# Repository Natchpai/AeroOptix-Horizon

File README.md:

**Flight controller for the AeroOptix Club aircraft, STM32H743 with an STM32F100 IO MCU**

> **Status:** `PRELIMINARY`
> **Board revision:** `A`
> **Baseline:** `NOT_ESTABLISHED`
> **KiCad:** `10.0.8`

> **Draft specification (rev 0.95, 2026-11-28): NOT FOR FABRICATION.** Everything below is a design target from the specification, not a verified result. Values not yet decided are shown as `TBD`.

## Overview

AeroOptix-Horizon is a custom PX4 flight controller with two MCUs. The STM32H743VIT6 runs the flight stack and drives the 4 tilt servo outputs. The STM32F100C8T6B runs px4io and drives the 4 ESC outputs, the 4 control-surface servo outputs, the safety switch and the output failsafe (DEC-050, DEC-051).

Pixhawk 6C and 6X are functional references only; their schematics and PCBs are not copied. H743 pins mostly follow `px4/fmu-v6c`, F100 pins follow `px4/io-v2` (DEC-014).

The team website, [natchpai.github.io/AeroOptix-Horizon](https://natchpai.github.io/AeroOptix-Horizon/), shows the block diagram, the MCU pinouts and the status, built from the design records.

## Key Features

- STM32H743VIT6 flight MCU and STM32F100C8T6B px4io MCU, linked over USART at 1.5 Mb/s
- 4 ESC outputs (MAIN 1 to 4) and 4 control-surface outputs (MAIN 5 to 8) on the F100, 4 tilt servo outputs (AUX 1 to 4) on the H743; 8 servo headers on an on-board 6 V rail, 3 spare outputs
- 2× ICM-45686 IMU on SPI; ICP-20100 and BMP581 barometers and IST8310 magnetometer on I2C
- 5 V input through a TPS2121 power mux (power module or USB), 3.3 V buck, separate LDO for the sensor VDD pins
- USB FS, microSD, debug access to both MCUs, BOOT0 push button on the H743

## Specifications

| Parameter | Specification |
|---|---|
| Main MCU | STM32H743VIT6 (DEC-001) |
| IO MCU | STM32F100C8T6B (px4io, DEC-002) |
| Clocks | H743 16 MHz, F100 24 MHz, both from CMOS oscillators (DEC-017, DEC-044) |
| Outputs | F100 MAIN 1 to 4: 4 ESCs (PWM, 1000 to 2000 µs); F100 MAIN 5 to 8: 4 control surfaces (50 Hz PWM); H743 AUX 1 to 4: 4 tilt servos; 3 spare (H743) (DEC-050, DEC-051, FUN-002, FUN-003, IF-017 to IF-019) |
| Sensors | 2× ICM-45686, ICP-20100 + BMP581 (BMP384 fallback), IST8310 (DEC-008, DEC-010, DEC-011) |
| Board input | 5 V, 4.5 to 5.5 V, 2 A source; power mux limit 1.5 A; overvoltage cut-off 5.5 to 6.2 V (PWR-010, DEC-029, DEC-030, DEC-036, DEC-055) |
| 3.3 V rails | `+3V3` buck, design current about 0.6 A (DEC-012, DEC-040); `+3V3A` LDO for the sensor VDD pins; sensor VDDIO on `+3V3` (DEC-043, DEC-027) |
| Servo supply | Two rails, `+VSERVO1` (4 tilt servos) and `+VSERVO2` (4 surface servos), 6 to 8.4 V each; the DS3235 above its 7.4 V rating is accepted (PWR-011, DEC-110, DEC-113). One UBEC per rail (DEC-114), each through a 1x3 header, CN804 and CN805; XT30 removed (DEC-111). Stall at 6 V about 8.4 A and 4.8 A per rail, `ESTIMATED`; one header pin per rail, rating not checked, accepted (DEC-113). Bulk 112 µF nominal per rail (DEC-097, DEC-109); SMF8.5A TVS per rail (DEC-112); copper and GND join set at layout (OPEN-021) |
| Board outline | Under 80 mm each side; exact outline `TBD` (MEC-001, OPEN-009) |
| Mounting | M3, 3.2 mm holes, soft mount; pattern `TBD` (MEC-002, OPEN-009) |
| Layers / stackup | Drawn, not decided: 4 copper layers, about 1.6 mm, 0.1 mm track and clearance (PCB-001 to PCB-005, OPEN-040) |
| Temperature | Parts rated −40 to +85 °C (ENV-001, DEC-020) |

*Specifications describe design targets unless explicitly identified as measured or verified results.*

## Project Status

**Current Phase:** `PRELIMINARY`

| Phase | Description |
|---|---|
| DRAFT | Schematic design in progress |
| PRELIMINARY | Schematic nearly complete; PCB design started |
| CHECK | Design mostly finalized; human-led verification |
| RELEASE | Human-approved design baseline released |

*The project owner declares the current phase. It does not independently establish design correctness or approval.*

### Project Workflow Diagram

```mermaid
flowchart LR
    A["DRAFT<br/>Schematic Design"]
    B["PRELIMINARY<br/>Schematic Finalization<br/>PCB Design"]
    C["CHECK<br/>Design Docs<br/>ERC / DRC<br/>Human Review"]
    D["RELEASE<br/>Approved Design<br/>Baseline Publication"]

    A --> B
    B --> C
    C --> D

    classDef inactive fill:#334155,color:#ffffff,stroke:#64748b
    classDef review fill:#b45309,color:#ffffff,stroke:#92400e
    classDef done fill:#15803d,color:#ffffff,stroke:#166534

    class A done
    class B review
    class C inactive
    class D inactive
```

> Slate: not started, Amber: current phase, Green: completed

The diagram is for reference only. It does not enforce gates or approve releases.

### Design progress

State of the saved KiCad files (2026-11-21 11:12 save, commit `3c111fc`). Sheets not listed have no parts. Part lists, references and save dates are in specification 4.2 "Schematic state", 4.3 and 4.6. Pin allocation `ALLOCATED`, not `VERIFIED` (P1 closed by the human owner, 2026-11-21).

| Area | State |
|---|---|
| Power sheet | Drawn; human ERC and a `sch-review` of the 2026-11-03 save are under Verification; LCSC codes on all resistors; PR1, CP2 and OV bottom resistors 5.1 kΩ, OV trip 5.51 to 6.21 V (DEC-055); MFR, MFR.P/N and LCSC filled on R101 to R115 (P2-021 done 2026-11-21; 1 % tolerance `ASSUMED`); DNP Plan B diodes D105 and D106 replace U101 when it is not fitted (DEC-108, OPEN-041). |
| MCU sheets | In capture; one shared reset with one button decided; B901 PTS815SJM250SMTRLFS checked against LCSC C2689510, reset bench check open (DEC-046, OPEN-026); BOOT0 push button B902 to `+3V3` with R202 10 kΩ to `GND`, and F100 PB2 (BOOT1) without a resistor (DEC-095); separate NRST nets for each MCU behind D201 and D301, joined at B901 (DEC-074); board LEDs driven straight from the pins, active low, 220 Ω (DEC-067); F100 px4io LEDs (blue, red, green) and 10 kΩ pull-ups on PA10 and PB11 (DEC-079); the six LEDs are now two RGB LEDs, D901 (H743) and D902 (F100) (DEC-115); microSD 10 kΩ pull-ups on CMD and DAT0 to DAT3, no card detect (DEC-078), 100 nF and 2.2 µF at the card supply (DEC-081); oscillator parts decided and their data meets both MCU HSE bypass limits (DEC-048, CMP-010); LCSC codes match the part numbers (CMP-010); U302 clock margins accepted (DEC-089); VREF+ tied to VDDA with 2.2 µF (DEC-049, DEC-063); F100 VDDA 22 Ω with 2.2 µF and 100 nF (DEC-101); no ESD on microSD (DEC-104); stub labels on unused pins kept (DEC-105); all allocated pins labelled with DEC-052 net names and every sheet pin matching its label; the INFO names accepted as drawn (OPEN-032 closed); resistors renumbered without gaps (spec rev 0.75); servo-rail divider on `conn-actuator` decided (DEC-066); H743 battery ADC inputs removed, battery data comes from the PM02D only (DEC-107). |
| Sensor sheets | In capture with all five sensors; IST8310 at 0x0C as strapped (DEC-047, closes OPEN-027). ICM-45686 RESV pin 7 not connected (DEC-082); BMP581 INT through 10 kΩ to `GND`, ICP-20100 INT not connected (DEC-083); ICP-20100 power-up order accepted, bench check (DEC-085). I2C2 pull-ups R501 and R502 2 kΩ, bus at 400 kHz (DEC-094, DEC-100); U503 placed as far as possible from the power parts (DEC-096). Address straps are direct ties, no strap resistors: AD0 and SDO through net ties NT501 and NT502 to `GND`, CAD0 and CAD1 to `GND`, BMP581 CSB to `+3V3`; addresses 0x63, 0x46, 0x0C (DEC-099). One 100 nF per sensor supply pin, ICM-45686 pins 7 and 9 not connected (DEC-103); IST8310 VPP floating (DEC-102). |
| USB and debug sheet | In capture; MFR, MFR.P/N and LCSC on every BOM part (OPEN-010 closed); CN602 (H743) JST-SH 6-pin in the Pixhawk Debug Mini order, no NRST, reset by B901 (DEC-065); F100 debug on test pads TP601 to TP606, with TP605 on `RESET_B` (DEC-075); USB-C CC resistors 5.1 kΩ; USB nets checked and no `VBUS` back-feed through U101 (P1-006); VBUS sense on PA9 through a 5.1 kΩ / 10 kΩ divider, so PA9 stays under 4 V when the MCU is unpowered (DEC-080); USB ESD is the ST USBLC6-2SC6, LCSC C7519 (DEC-084); the `VBUS` `PWR_FLAG` stays on the power sheet (DEC-105). |
| External connectors | Drawn, not decided (spec 4.2): `conn-peripherals` (TELEM 1 and 2, I2C4, rangefinder, GPS1) linked to the MCU sheets by sheet pins; `conn-actuator` with MAIN 1 to 4 ESC headers (no + pin), AUX 1 to 4 on `+VSERVO1` and MAIN 5 to 8 on `+VSERVO2`, a 1x3 UBEC header per rail (CN804, CN805), bulk capacitors, a TVS and a sense divider per rail (DEC-110 to DEC-113). Decided 2026-11-19: C803 (C801 since the 2026-11-22 10:23 save) 68 µF 16 V tantalum (DEC-058) and D807 SMF7.5A unidirectional TVS (DEC-059; SMF8.5A with D808 since DEC-112). RC IN drawn (2026-11-19 15:25 save): SP3031-01ETG ESD (D708 since the 23:17 save; DEC-071), R715 22 Ω (R714 before the 16:03 save) and the U303 SN74LVC1G34DCKR buffer to F100 PA8 (DEC-056, DEC-057); CN706 is a 1x3 2.54 mm header since the 2026-11-20 save, with pin 1 PPM, 2 `+5V`, 3 `GND`, kept as drawn (DEC-098, amends DEC-072). 100 kΩ pull-downs on all 15 PWM lines (DEC-073). Spare outputs: 22 Ω series, pull-downs and pads CN707 to CN710 drawn (DEC-069, DEC-076). Second 68 µF T495 on `+6V` (DEC-097; C802 since the 10:23 save). 4 × 22 µF 25 V X7R 1210 (C803 to C806) add low-ESR bulk, 224 µF nominal (DEC-109); the servo-rail 100 nF is C809. Connector pinouts match DS-009; CN704 silkscreen left (OPEN-023). |
| PCB | Updated from the schematic by the human owner (2026-11-21, commit `eec3593`, adds D105 and D106; 2026-11-22 09:23 save: Description fields and BOM exclusion on the test pads, solder pads and net ties); not yet updated from the 2026-11-22 10:23 schematic (C801 to C806 and C809, P3-013) or the 2026-11-24 servo rail split (P3-014). First import 2026-11-20 (commit `a70e6cc`, 9 placed inside the working area then); no routing. 4-layer stackup and board rules drawn, not decided (OPEN-040). The 80 × 80 mm `Edge.Cuts` rectangle is a working area, not the board outline (OPEN-009). |
| Library | Project parts for the parts in use. Sensor footprints: IST8310 and BMP581 confirmed by the human owner, with a 30 µm solder mask margin on purpose; ICP-20100 and ICM-45686 match the datasheet body, pitch and pad numbers and are kept without the TDK land-pattern app notes (DEC-086). New: Amass XT30PW-M symbol, footprint and 3D model. MFR and MFR.P/N on the 20 placed, fully specified library symbols; descriptions in one pattern (2026-11-20). |

## Hardware Design

### Architecture

| Block | Role |
|---|---|
| H743 main controller | Flight stack and interface host; 4 tilt servo outputs (AUX 1 to 4) |
| F100 IO controller | px4io: 4 ESC and 4 control-surface outputs (MAIN 1 to 8), safety switch and LED, servo rail sense, output failsafe (DEC-051) |
| Sensors | 2 IMU on SPI1 and SPI4; 2 barometers and the magnetometer on I2C2 |
| External I/O | SiK telemetry radio, RC receiver (PPM, F100), GPS and compass, air-data sensor, rangefinder, power module, motors (one 4in1 ESC), spare output pads, microSD, GPS module buzzer (no board buzzer), LEDs (DEC-053, DEC-054, DEC-056, DEC-057, DEC-068, DEC-069) |
| USB / debug | USB FS; H743 debug connector CN602, console + SWD in the Pixhawk Debug Mini order, no NRST (IF-045, DEC-065); F100 console + SWD on test pads TP601 to TP606 (IF-051, DEC-075) |
| Power | 5 V input, 3.3 V buck, sensor LDO, two servo rails (6 to 8.4 V) |

### External interfaces

Interface allocations agreed with the software team (DEC-014, DEC-018) are in specification sections 3.4 and 3.5 ([spec](hardware/AO-Horizon/documents/design/AO-HORIZON_SPEC_EN.md)) and the [pin allocation record](hardware/AO-Horizon/documents/design/AO-HORIZON_PIN_ALLOCATION_EN.md); connector pinouts are not checked yet (OPEN-023).

### Design Considerations

- IO MCU and clocks: STM32F100C8T6B for px4io at 24 MHz; CMOS oscillators with HSE bypass set in firmware (DEC-002, DEC-017, DEC-044, DEC-045).
- USB power: bench supply only, needs a USB-C port above 1 A; the power module has priority (DEC-031 to DEC-034, DEC-038).
- Actuator outputs and H743 failure: the ESCs run timer PWM from the F100 (no DShot). When the H743 stops, the F100 turns the motors off and sets the surfaces to a fixed position, with no landing; the tilt servos on the H743 hold their last angle (DEC-050, DEC-051). Whether the ESCs stop on the failsafe pulse is open (OPEN-017).
- Net names: a signal that leaves its sheet starts with its port, plus the MCU peripheral on peripheral pins (for example `GPS1_UART2_TX`); `H7_`/`F1_` on nets local to an MCU sheet; `_B` for active-low. Bus names and port numbering are the designer's choice (DEC-052, partly drawn).
- Sensor sourcing: ICP-20100 is EOL, BMP581 stock is short (OPEN-004).
- Sensor use and vibration: sample rates, calibration and how PX4 uses the redundant sensors are software work, deferred (DEC-061). No numeric vibration limit for revision 1: the soft mount is the control, checked with PX4 vibration metrics in the flight logs (DEC-062).
- Firmware: owned by the software team, PX4 v1.16.2 based on `px4/fmu-v6c` (DEC-014).

## Verification

| Check | Result | Evidence |
|---|---|---|
| Schematic ERC | Whole schematic, report 2026-11-22 10:24 (after the 10:23 `conn-actuator` save): 0 errors, 0 warnings, 13 sheets | [`AO-Horizon-erc.rpt`](hardware/AO-Horizon/documents/verification/AO-Horizon-erc.rpt), run by the human owner. An ERC pass is not a proof of correctness |
| Schematic review | Power sheet (2026-11-03 save); connector and actuator sheets (2026-11-19 12:49 save); MCU sheets (2026-11-20, commit `6b01a14`); sensor and USB sheets (2026-11-20 14:29 save); user interface sheet (2026-11-21, commit `7768105`). One row per sheet in the [review record](hardware/AO-Horizon/documents/verification/AO-HORIZON_SCH_REVIEW_RECORD_EN.md), signed by the human owner 2026-11-21 | `sch-review`, spec 4.3 and 4.2; findings open (OPEN-021, OPEN-023); OPEN-038 closed. MCU sheets: the PA9 VBUS MAJOR is fixed (DEC-080); MINOR and INFO findings in `todo.md`. Sensor and USB sheets: no connectivity defect; findings closed by DEC-081 to DEC-085. All 12 bus links traced with the KiCad netlist (16:03 save): every member reaches its allocated pin; the spare outputs reach no pad yet |
| Pin allocation review | Signed off by the human owner, 2026-11-21: `ALLOCATED`, not `VERIFIED` | [Pin allocation](hardware/AO-Horizon/documents/design/AO-HORIZON_PIN_ALLOCATION_EN.md) section 6 |
| PCB DRC | `NOT_VERIFIED` | Not run; PCB not routed |
| BOM / footprint review | `NOT_VERIFIED` | `TBD` |
| Prototype functional test | `NOT_VERIFIED` | Bench tasks P4-012 to P4-015 open |

## Open Items

The specification tracks every open item in section 8.2 of the [specification](hardware/AO-Horizon/documents/design/AO-HORIZON_SPEC_EN.md). Top items now:

- ESC (Tekko32 with AM32): stop on the F100 failsafe pulse, PWM rate, 8-pin pinout, BEC and PWM level (OPEN-017)
- RC IN: U303 inputs take 5.5 V (ti.com); FS-iA6B PPM level, RC-loss behavior and receiver lead are bench and team items (OPEN-034, P4-016)
- PCB stackup and board rules drawn, not decided; fabricator confirmation needed (OPEN-040, P3-010)
- Board outline, mounting and cable entry (OPEN-009, P3-001)
- Servo power: two rails, 6 to 8.4 V (DEC-110 to DEC-113); ERC and PCB update for the split (P3-014); copper width and the servo/logic GND join set at layout (OPEN-021, P3-003)
- Actuator headers: keep the ESC and RC IN headers apart from the servo headers, at placement and on the silkscreen (OPEN-031, P3-002, P3-007)
- Sensors: ICP-20100 EOL, BMP581 stock and IST8310 lifecycle (OPEN-004, P3-007)
- Bench checks: reset paths (OPEN-026, P4-002) and sensor power-up order (OPEN-011, P4-015)
- Firmware: HSE bypass on both MCUs (OPEN-028, P2-005)

## How we work

1. A human engineer makes every design decision and declares the phase; decisions go into the specification first.
2. The saved KiCad files are the design authority; the Markdown records describe them.
3. Values carry evidence labels (`VERIFIED`, `ASSUMED`, `ESTIMATED`, `NOT_VERIFIED`). ERC and DRC are evidence, not proof.
4. Changes go through `dev` and a pull request to `main`, with Conventional Commits.

Claude Code support (rules, skills, file protection) is in `.claude/` and `CLAUDE.md`.

## Repository Structure

```text
AeroOptix-Horizon/
├── hardware/AO-Horizon/
│   ├── AO-Horizon.kicad_pro           # KiCad project
│   ├── *.kicad_sch, AO-Horizon.kicad_pcb
│   ├── library/                       # Project symbols, footprints, 3D models
│   ├── documents/design/              # Specification, checklist, design records
│   ├── documents/                     # Reference, manufacturing, schematic, verification, images
│   └── templates/                     # Worksheets, theme, fab/assembly notes
├── web/                               # Team website, built from the records
├── assets/                            # README title image
├── .claude/, .github/                 # Claude Code config; PR template and Pages workflow
├── CLAUDE.md, CHANGELOG.md, LICENSE
└── README.md
```

## Documentation

| Resource | Description |
|---|---|
| [Specification](hardware/AO-Horizon/documents/design/AO-HORIZON_SPEC_EN.md) | Requirements, decisions, schematic and library state, open items |
| [Execution checklist](hardware/AO-Horizon/documents/design/AO-HORIZON_EXECUTION_CHECKLIST_EN.md) | Work plan and evidence tracker |
| [Power budget](hardware/AO-Horizon/documents/design/AO-HORIZON_POWER_BUDGET_EN.md) | Rail loads, tolerances, thermal margin and protection |
| [Power mux notes](hardware/AO-Horizon/documents/design/AO-HORIZON_POWER_MUX_NOTES_EN.md) | TPS2121 modes and resistor calculations |
| [Pin allocation](hardware/AO-Horizon/documents/design/AO-HORIZON_PIN_ALLOCATION_EN.md) | H743 and F100 pin allocation |
| [Software clock note](hardware/AO-Horizon/documents/design/AO-HORIZON_SW_CLOCK_NOTE_EN.md) | HSE bypass request to the software team (DEC-045, P1-017) |
| [Design records index](hardware/AO-Horizon/documents/design/README.md) | All other records: sensor selection, pinmap review and decisions, integration questions, sourcing |
| [Team website](https://natchpai.github.io/AeroOptix-Horizon/) | Block diagram, MCU pinouts and status ([source](web/README.md)) |

## License

Copyright (c) 2026 AeroOptix Club.

The hardware design files are licensed under CERN-OHL-S-2.0.

The complete license text is available in:

[CERN Open Hardware Licence Version 2 - Strongly Reciprocal](LICENSE)

## Changelog

See [`CHANGELOG.md`](CHANGELOG.md).

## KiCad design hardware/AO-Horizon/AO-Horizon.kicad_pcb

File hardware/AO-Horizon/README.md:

# AO-Horizon KiCad Project

KiCad 10 project for the AeroOptix-Horizon flight controller. Project status, decisions and open items are in the [repository README](../../README.md) and the [specification](documents/design/AO-HORIZON_SPEC_EN.md).

The saved native KiCad files in this folder are the design authority.

## Layout

- `AO-Horizon.kicad_pro`, `AO-Horizon.kicad_sch`, `AO-Horizon.kicad_pcb`: project, root schematic and PCB.
- `top_hierarchical.kicad_sch`, `block_diagram.kicad_sch`, `power_supplies.kicad_sch`, `revision_history.kicad_sch`: schematic sheets.
- `sym-lib-table`, `fp-lib-table`: project library tables. Every entry points into `library/` through `${KIPRJMOD}`.
- `library/`: project symbols (`symbols/0_<Family>.kicad_symdir`), footprints (`footprints/0_<Family>.pretty`) and 3D models (`3D/<Family>/`).
- `documents/`: design records (`design/`), images, manufacturing, schematic and verification outputs.
- `templates/`: title-block worksheets, board theme, and fabrication, assembly and impedance notes.

KiCad backups (`AO-Horizon-backups/`, `*.bak`) are git-ignored and are not design sources.

## Directory tree

```text
AO-Horizon/
├── AO-Horizon.kicad_pro
├── AO-Horizon.kicad_sch
├── AO-Horizon.kicad_pcb
├── top_hierarchical.kicad_sch
├── block_diagram.kicad_sch
├── power_supplies.kicad_sch
├── revision_history.kicad_sch
├── sym-lib-table
├── fp-lib-table
├── documents/
│   ├── design/            # Specification, checklist and design records
│   ├── images/            # Documentation images and logos
│   ├── manufacturing/     # Assembly (BOM) and fabrication (Gerbers) outputs
│   ├── schematic/         # Schematic outputs
│   └── verification/      # Review reports and test evidence
├── library/
│   ├── symbols/           # 0_<Family>.kicad_symdir
│   ├── footprints/        # 0_<Family>.pretty
│   └── 3D/                # <Family>/*.step
├── templates/             # Worksheets, theme, notes
└── README.md
```

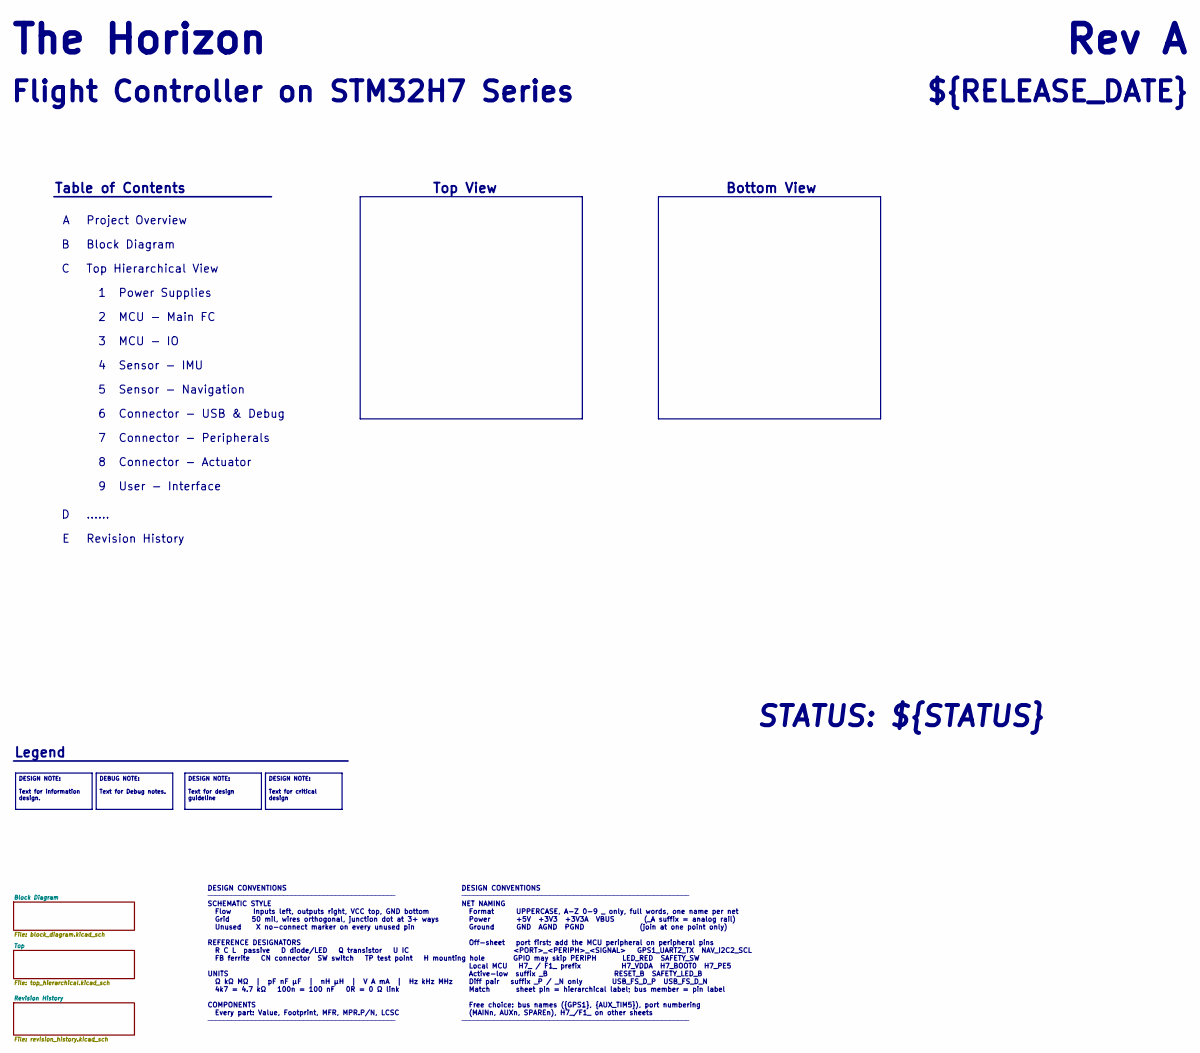
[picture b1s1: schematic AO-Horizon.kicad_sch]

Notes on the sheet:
Rev ${REVISION}
......
DESIGN CONVENTIONS ─────────────────────────────────────────────── SCHEMATIC STYLE Flow Inputs left, outputs right, VCC top, GND bottom Grid 50 mil, wires orthogonal, junction dot at 3+ ways Unused X no-connect marker on every unused pin REFERENCE DESIGNATORS R C L passive D diode/LED Q transistor 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
Connector - USB & Debug
Connector - Peripherals
${RELEASE_DATE}
MCU - Main FC
Legend
Sensor - IMU
Flight Controller on STM32H7 Series
Project Overview
Table of Contents
Power Supplies
DESIGN CONVENTIONS ───────────────────────────────────────────────────────── NET NAMING Format UPPERCASE, A-Z 0-9 _ only, full words, one name per net Power +5V +3V3 +3V3A VBUS (_A suffix = analog rail) Ground GND AGND PGND (join at one point only) Off-sheet port first; add the MCU peripheral on pe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
Sensor - Navigation
MCU - IO
Bottom View
Top Hierarchical View
The Horizon
Revision History
STATUS: ${STATUS}
Top View
User - Interface
Block Diagram
Connector - Actuator
DESIGN NOTE: Text for information design.
DEBUG NOTE: Text for Debug notes.
DESIGN NOTE: Text for critical design
DESIGN NOTE: Text for design guideline

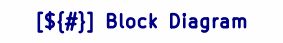
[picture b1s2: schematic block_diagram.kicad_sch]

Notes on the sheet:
[${#}] ${COMMENT1}

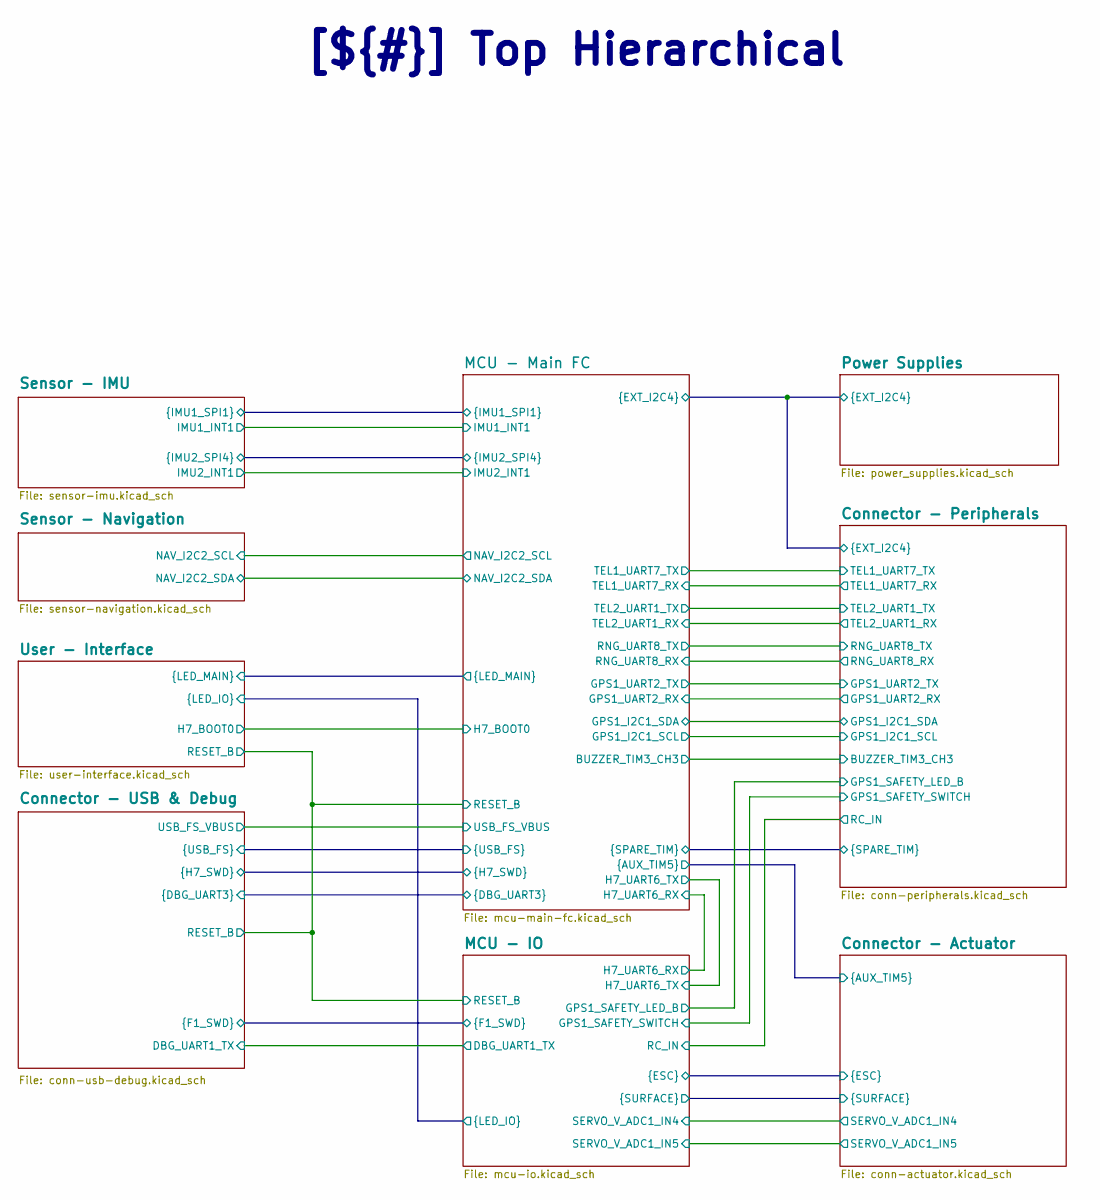
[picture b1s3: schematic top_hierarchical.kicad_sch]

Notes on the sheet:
[${#}] ${COMMENT1}

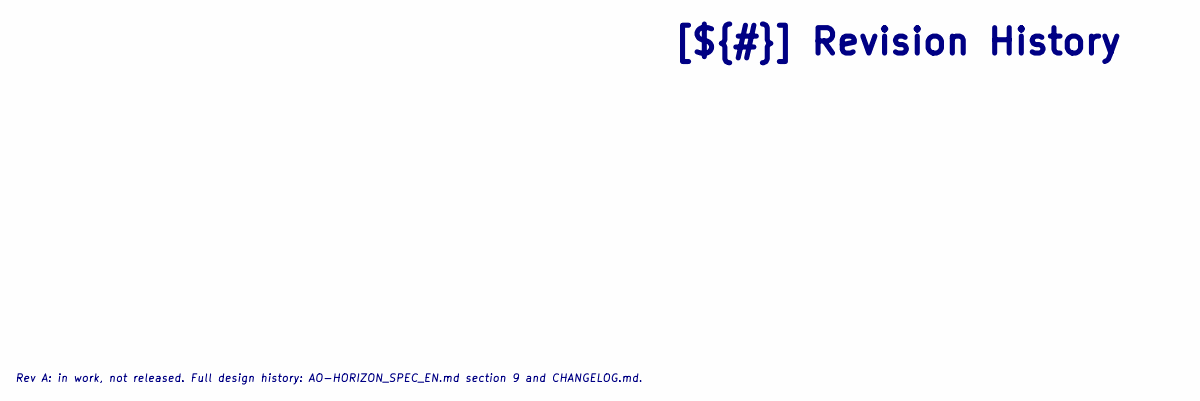
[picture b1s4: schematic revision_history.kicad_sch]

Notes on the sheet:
Rev A: in work, not released. Full design history: AO-HORIZON_SPEC_EN.md section 9 and CHANGELOG.md.
[${#}] ${COMMENT1}

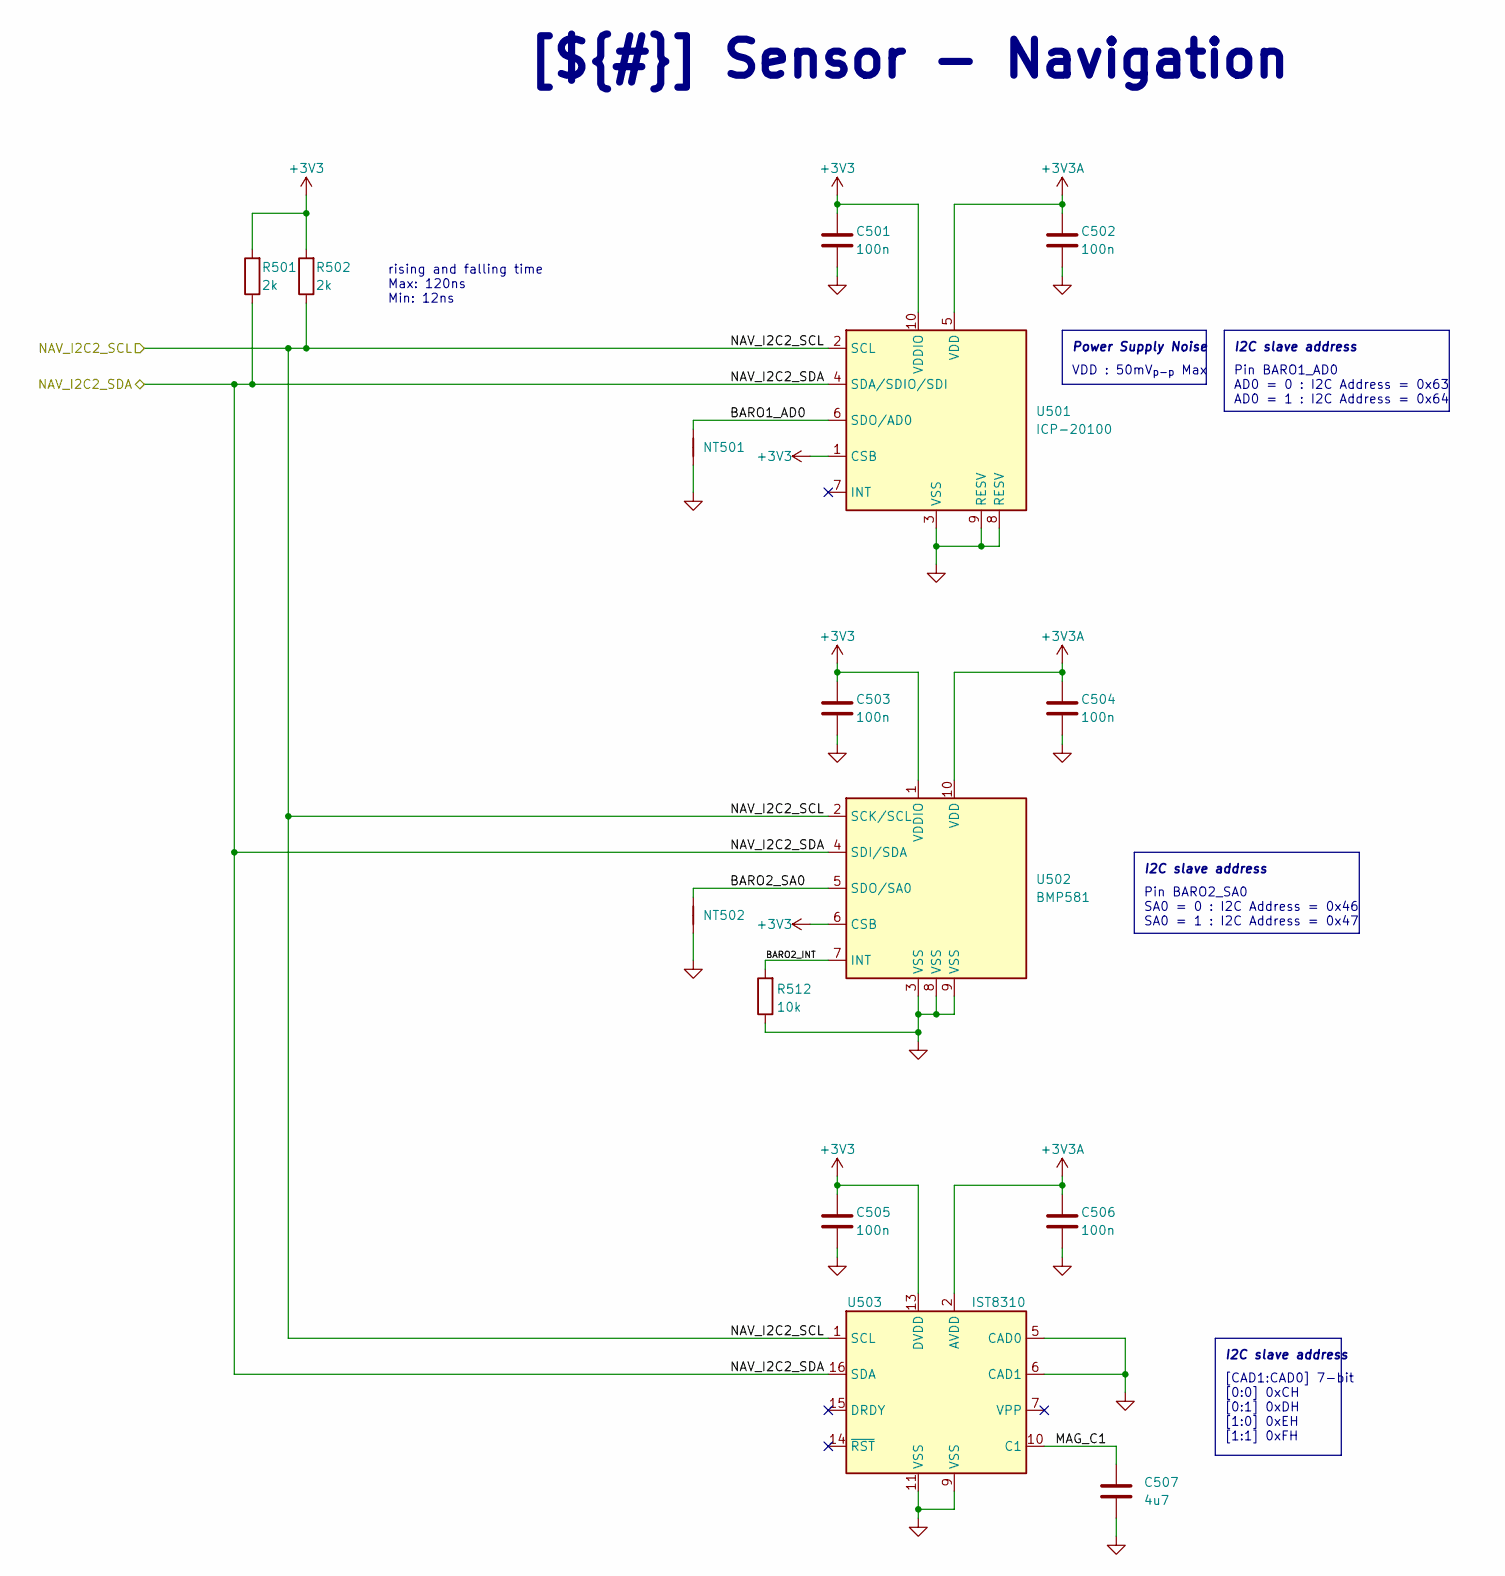
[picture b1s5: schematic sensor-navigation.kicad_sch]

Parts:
C501, C502, C503, C504, C505, C506: 100n; C_0402_1005Metric_NomDensity; MFR.P/N GCM155R71H104KE02D; LCSC C85858
C507: 4u7; C_0603_1608Metric_NomDensity; MFR.P/N GRM188Z71C475KE21D; LCSC C389010
NT501, NT502: GND; NetTie-2_SMD_Pad0.15mm
R501, R502: 2k; R_0402_1005Metric_NomDensity; MFR.P/N RC0402FR-072KL; LCSC C60488
R512: 10k; R_0402_1005Metric_NomDensity; MFR.P/N AC0402FR-0710KL; LCSC C144807
U501: ICP-20100; ST_HLGA-10_2x2mm_P0.5mm_LayoutBorder3x2y; MFR.P/N ICP-20100; LCSC C5343527
U502: BMP581; Bosch_LGA-10_2x2mm_P0.5mm_LayoutBorder3x2y; MFR.P/N BMP581; LCSC C5362283
U503: IST8310; LGA-16_3x3mm_P0.5mm; MFR.P/N IST8310; LCSC C2683055

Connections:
+3V3: C501.1, C503.1, C505.1, R501.2, R502.2, U501.1 (CSB), U501.10 (VDDIO), U502.1 (VDDIO), U502.6 (CSB), U503.13 (DVDD); also elsewhere on the board
+3V3A: C502.1, C504.1, C506.1, U501.5 (VDD), U502.10 (VDD), U503.2 (AVDD); also elsewhere on the board
/Top/MCU - Main FC/NAV_I2C2_SCL: R502.1, U501.2 (SCL), U502.2 (SCK/SCL), U503.1 (SCL); also elsewhere on the board
/Top/MCU - Main FC/NAV_I2C2_SDA: R501.1, U501.4 (SDA/SDIO/SDI), U502.4 (SDI/SDA), U503.16 (SDA); also elsewhere on the board
/Top/Sensor - Navigation/BARO1_AD0: NT501.1, U501.6 (SDO/AD0)
/Top/Sensor - Navigation/BARO2_INT: R512.2, U502.7 (INT)
/Top/Sensor - Navigation/BARO2_SA0: NT502.1, U502.5 (SDO/SA0)
/Top/Sensor - Navigation/MAG_C1: C507.1, U503.10 (C1)
GND: C501.2, C502.2, C503.2, C504.2, C505.2, C506.2, C507.2, NT501.2, NT502.2, R512.1, U501.3 (VSS), U501.8 (RESV), U501.9 (RESV), U502.3 (VSS), U502.8 (VSS), U502.9 (VSS), U503.5 (CAD0), U503.6 (CAD1), U503.9 (VSS), U503.11 (VSS); also elsewhere on the board

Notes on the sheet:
Power Supply Noise
VDD : 50mV_{p-p} Max
[${#}] ${COMMENT1}
I2C slave address
rising and falling time Max: 120ns Min: 12ns
Pin BARO1_AD0 AD0 = 0 : I2C Address = 0x63 AD0 = 1 : I2C Address = 0x64
Pin BARO2_SA0 SA0 = 0 : I2C Address = 0x46 SA0 = 1 : I2C Address = 0x47
[CAD1:CAD0] 7-bit [0:0] 0xCH [0:1] 0xDH [1:0] 0xEH [1:1] 0xFH

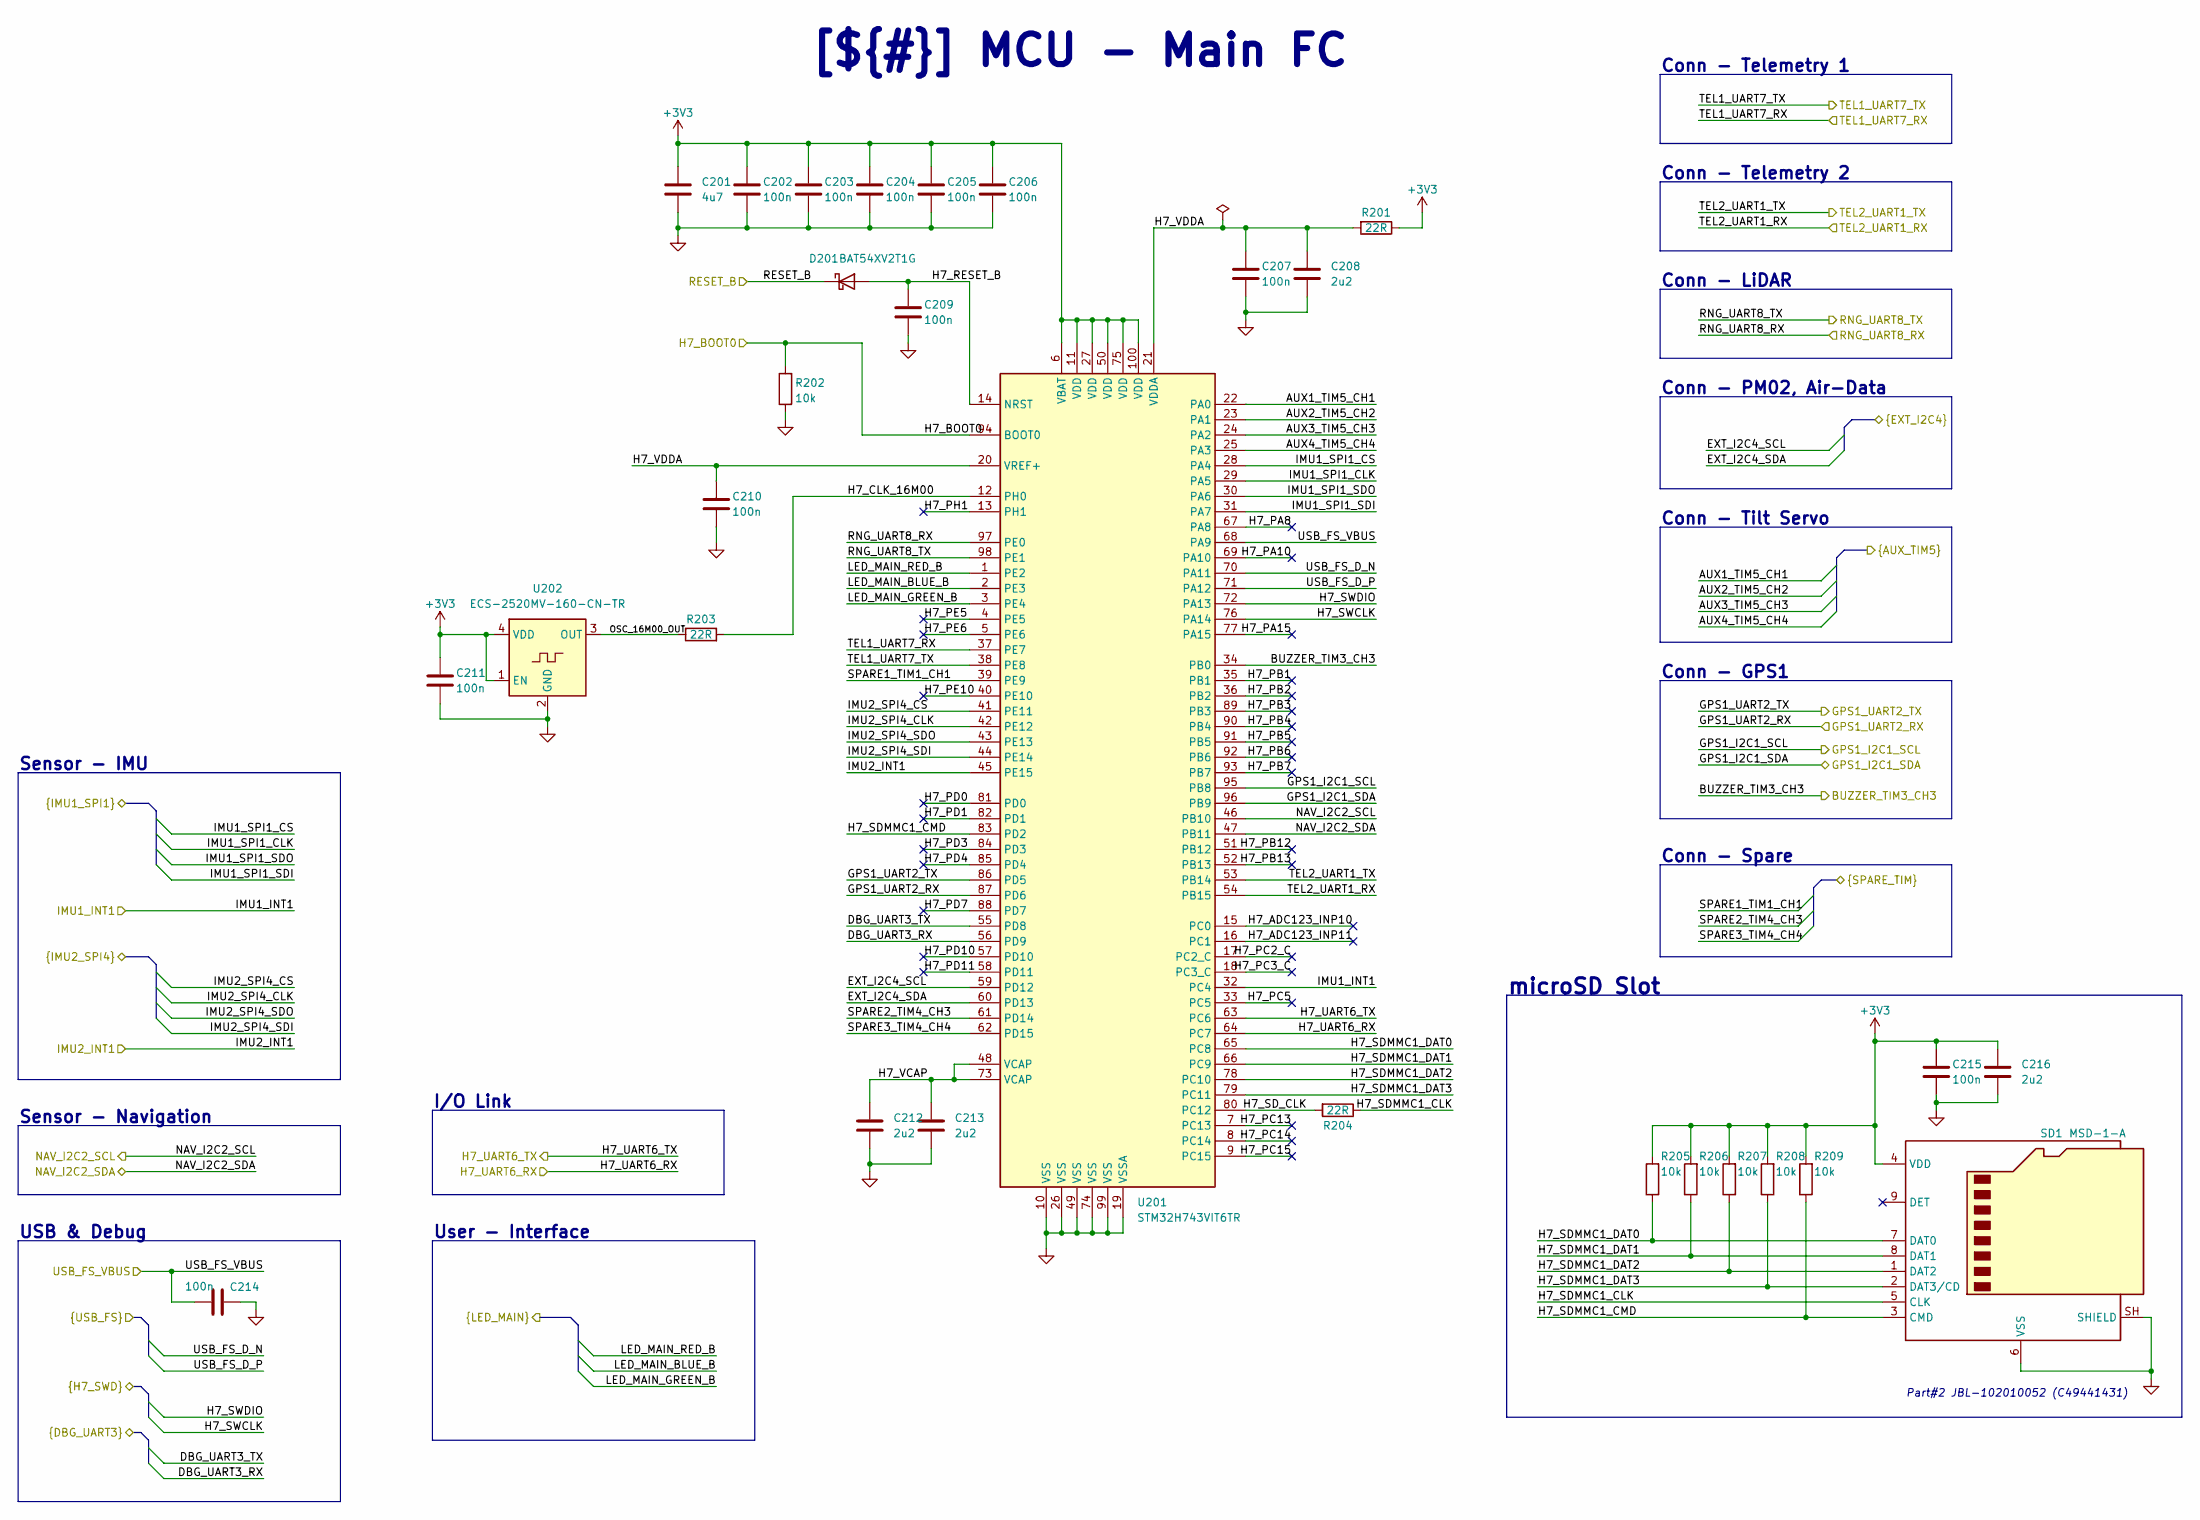
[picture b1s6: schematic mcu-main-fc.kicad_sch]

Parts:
C201: 4u7; C_0603_1608Metric_NomDensity; MFR.P/N GRM188Z71C475KE21D; LCSC C389010
C202, C203, C204, C205, C206, C207, C209, C210, C211, C214, C215: 100n; C_0402_1005Metric_NomDensity; MFR.P/N GCM155R71H104KE02D; LCSC C85858
C208, C212, C213, C216: 2u2; C_0603_1608Metric_NomDensity; MFR.P/N GRM188Z71C225KE43D; LCSC C576485
D201: BAT54XV2T1G; D_SOD-523; MFR.P/N BAT54XV2T1G; LCSC C81572
R201, R203, R204: 22R; R_0402_1005Metric_NomDensity; MFR.P/N RC0402FR-0722RL; LCSC C114765
R202, R205, R206, R207, R208, R209: 10k; R_0402_1005Metric_NomDensity; MFR.P/N AC0402FR-0710KL; LCSC C144807
SD1: MSD-1-A; CUI_microSD_MSD-1-A; MFR.P/N MSD-1-A; LCSC C20619272
U201: STM32H743VIT6TR; LQFP-100_14x14mm_P0.5mm; MFR.P/N STM32H743VIT6TR; LCSC C5271084
U202: ECS-2520MV-160-CN-TR; Oscillator_SMD_ECS_2520MV-4Pin_2.5x2.0mm; MFR.P/N ECS-2520MV-160-CN-TR; LCSC C405461

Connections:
+3V3: C201.1, C202.1, C203.1, C204.1, C205.1, C206.1, C211.1, C215.1, C216.1, R201.1, R205.2, R206.2, R207.2, R208.2, R209.2, SD1.4 (VDD), U201.6 (VBAT), U201.11 (VDD), U201.27 (VDD), U201.50 (VDD), U201.75 (VDD), U201.100 (VDD), U202.1 (EN), U202.4 (VDD); also elsewhere on the board
/Top/Connector - Actuator/AUX1_TIM5_CH1: U201.22 (PA0); also elsewhere on the board
/Top/Connector - Actuator/AUX2_TIM5_CH2: U201.23 (PA1); also elsewhere on the board
/Top/Connector - Actuator/AUX3_TIM5_CH3: U201.24 (PA2); also elsewhere on the board
/Top/Connector - Actuator/AUX4_TIM5_CH4: U201.25 (PA3); also elsewhere on the board
/Top/Connector - Peripherals/EXT_I2C4_SCL: U201.59 (PD12); also elsewhere on the board
/Top/Connector - Peripherals/EXT_I2C4_SDA: U201.60 (PD13); also elsewhere on the board
/Top/Connector - Peripherals/GPS1_I2C1_SCL: U201.95 (PB8); also elsewhere on the board
/Top/Connector - Peripherals/GPS1_I2C1_SDA: U201.96 (PB9); also elsewhere on the board
/Top/Connector - Peripherals/GPS1_UART2_RX: U201.87 (PD6); also elsewhere on the board
/Top/Connector - Peripherals/GPS1_UART2_TX: U201.86 (PD5); also elsewhere on the board
/Top/Connector - Peripherals/RNG_UART8_RX: U201.97 (PE0); also elsewhere on the board
/Top/Connector - Peripherals/RNG_UART8_TX: U201.98 (PE1); also elsewhere on the board
/Top/Connector - Peripherals/SPARE1_TIM1_CH1: U201.39 (PE9); also elsewhere on the board
/Top/Connector - Peripherals/SPARE2_TIM4_CH3: U201.61 (PD14); also elsewhere on the board
/Top/Connector - Peripherals/SPARE3_TIM4_CH4: U201.62 (PD15); also elsewhere on the board
/Top/Connector - Peripherals/TEL1_UART7_RX: U201.37 (PE7); also elsewhere on the board
/Top/Connector - Peripherals/TEL1_UART7_TX: U201.38 (PE8); also elsewhere on the board
/Top/Connector - Peripherals/TEL2_UART1_RX: U201.54 (PB15); also elsewhere on the board
/Top/Connector - Peripherals/TEL2_UART1_TX: U201.53 (PB14); also elsewhere on the board
/Top/Connector - USB & Debug/DBG_UART3_RX: U201.56 (PD9); also elsewhere on the board
/Top/Connector - USB & Debug/DBG_UART3_TX: U201.55 (PD8); also elsewhere on the board
/Top/Connector - USB & Debug/H7_SWCLK: U201.76 (PA14); also elsewhere on the board
/Top/Connector - USB & Debug/H7_SWDIO: U201.72 (PA13); also elsewhere on the board
/Top/Connector - USB & Debug/RESET_B: D201.1 (K); also elsewhere on the board
/Top/Connector - USB & Debug/USB_FS_D_N: U201.70 (PA11); also elsewhere on the board
/Top/Connector - USB & Debug/USB_FS_D_P: U201.71 (PA12); also elsewhere on the board
/Top/Connector - USB & Debug/USB_FS_VBUS: C214.2, U201.68 (PA9); also elsewhere on the board
/Top/MCU - Main FC/BUZZER_TIM3_CH3: U201.34 (PB0); also elsewhere on the board
/Top/MCU - Main FC/H7_ADC123_INP10: U201.15 (PC0)
/Top/MCU - Main FC/H7_ADC123_INP11: U201.16 (PC1)
/Top/MCU - Main FC/H7_BOOT0: R202.2, U201.94 (BOOT0); also elsewhere on the board
/Top/MCU - Main FC/H7_CLK_16M00: R203.2, U201.12 (PH0)
/Top/MCU - Main FC/H7_PA8: U201.67 (PA8)
/Top/MCU - Main FC/H7_PA10: U201.69 (PA10)
/Top/MCU - Main FC/H7_PA15: U201.77 (PA15)
/Top/MCU - Main FC/H7_PB1: U201.35 (PB1)
/Top/MCU - Main FC/H7_PB2: U201.36 (PB2)
/Top/MCU - Main FC/H7_PB3: U201.89 (PB3)
/Top/MCU - Main FC/H7_PB4: U201.90 (PB4)
/Top/MCU - Main FC/H7_PB5: U201.91 (PB5)
/Top/MCU - Main FC/H7_PB6: U201.92 (PB6)
/Top/MCU - Main FC/H7_PB7: U201.93 (PB7)
/Top/MCU - Main FC/H7_PB12: U201.51 (PB12)
/Top/MCU - Main FC/H7_PB13: U201.52 (PB13)
/Top/MCU - Main FC/H7_PC2_C: U201.17 (PC2_C)
/Top/MCU - Main FC/H7_PC3_C: U201.18 (PC3_C)
/Top/MCU - Main FC/H7_PC5: U201.33 (PC5)
/Top/MCU - Main FC/H7_PC13: U201.7 (PC13)
/Top/MCU - Main FC/H7_PC14: U201.8 (PC14)
/Top/MCU - Main FC/H7_PC15: U201.9 (PC15)
/Top/MCU - Main FC/H7_PD0: U201.81 (PD0)
/Top/MCU - Main FC/H7_PD1: U201.82 (PD1)
/Top/MCU - Main FC/H7_PD3: U201.84 (PD3)
/Top/MCU - Main FC/H7_PD4: U201.85 (PD4)
/Top/MCU - Main FC/H7_PD7: U201.88 (PD7)
/Top/MCU - Main FC/H7_PD10: U201.57 (PD10)
/Top/MCU - Main FC/H7_PD11: U201.58 (PD11)
/Top/MCU - Main FC/H7_PE5: U201.4 (PE5)
/Top/MCU - Main FC/H7_PE6: U201.5 (PE6)
/Top/MCU - Main FC/H7_PE10: U201.40 (PE10)
/Top/MCU - Main FC/H7_PH1: U201.13 (PH1)
/Top/MCU - Main FC/H7_RESET_B: C209.1, D201.2 (A), U201.14 (NRST)
/Top/MCU - Main FC/H7_SDMMC1_CLK: R204.1, SD1.5 (CLK)
/Top/MCU - Main FC/H7_SDMMC1_CMD: R209.1, SD1.3 (CMD), U201.83 (PD2)
/Top/MCU - Main FC/H7_SDMMC1_DAT0: R205.1, SD1.7 (DAT0), U201.65 (PC8)
/Top/MCU - Main FC/H7_SDMMC1_DAT1: R206.1, SD1.8 (DAT1), U201.66 (PC9)
/Top/MCU - Main FC/H7_SDMMC1_DAT2: R207.1, SD1.1 (DAT2), U201.78 (PC10)
/Top/MCU - Main FC/H7_SDMMC1_DAT3: R208.1, SD1.2 (DAT3/CD), U201.79 (PC11)
/Top/MCU - Main FC/H7_SD_CLK: R204.2, U201.80 (PC12)
/Top/MCU - Main FC/H7_UART6_RX: U201.64 (PC7); also elsewhere on the board
/Top/MCU - Main FC/H7_UART6_TX: U201.63 (PC6); also elsewhere on the board
/Top/MCU - Main FC/H7_VCAP: C212.1, C213.1, U201.48 (VCAP), U201.73 (VCAP)
/Top/MCU - Main FC/H7_VDDA: C207.1, C208.1, C210.1, R201.2, U201.20 (VREF+), U201.21 (VDDA)
/Top/MCU - Main FC/IMU1_INT1: U201.32 (PC4); also elsewhere on the board
/Top/MCU - Main FC/IMU1_SPI1_CLK: U201.29 (PA5); also elsewhere on the board
/Top/MCU - Main FC/IMU1_SPI1_CS: U201.28 (PA4); also elsewhere on the board
/Top/MCU - Main FC/IMU1_SPI1_SDI: U201.31 (PA7); also elsewhere on the board
/Top/MCU - Main FC/IMU1_SPI1_SDO: U201.30 (PA6); also elsewhere on the board
/Top/MCU - Main FC/IMU2_INT1: U201.45 (PE15); also elsewhere on the board
/Top/MCU - Main FC/IMU2_SPI4_CLK: U201.42 (PE12); also elsewhere on the board
/Top/MCU - Main FC/IMU2_SPI4_CS: U201.41 (PE11); also elsewhere on the board
/Top/MCU - Main FC/IMU2_SPI4_SDI: U201.44 (PE14); also elsewhere on the board
/Top/MCU - Main FC/IMU2_SPI4_SDO: U201.43 (PE13); also elsewhere on the board
/Top/MCU - Main FC/LED_MAIN_BLUE_B: U201.2 (PE3); also elsewhere on the board
/Top/MCU - Main FC/LED_MAIN_GREEN_B: U201.3 (PE4); also elsewhere on the board
/Top/MCU - Main FC/LED_MAIN_RED_B: U201.1 (PE2); also elsewhere on the board
/Top/MCU - Main FC/NAV_I2C2_SCL: U201.46 (PB10); also elsewhere on the board
/Top/MCU - Main FC/NAV_I2C2_SDA: U201.47 (PB11); also elsewhere on the board
/Top/MCU - Main FC/OSC_16M00_OUT: R203.1, U202.3 (OUT)
GND: C201.2, C202.2, C203.2, C204.2, C205.2, C206.2, C207.2, C208.2, C209.2, C210.2, C211.2, C212.2, C213.2, C214.1, C215.2, C216.2, R202.1, SD1.6 (VSS), SD1.SH (SHIELD), U201.10 (VSS), U201.19 (VSSA), U201.26 (VSS), U201.49 (VSS), U201.74 (VSS), U201.99 (VSS), U202.2 (GND); also elsewhere on the board

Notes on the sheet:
USB & Debug
User - Interface
Sensor - Navigation
microSD Slot
Conn - GPS1
Conn - Spare
Conn - LiDAR
Conn - PM02, Air-Data
Conn - Tilt Servo
Conn - Telemetry 2
Part#2 JBL-102010052 (C49441431)
I/O Link
[${#}] ${COMMENT1}
Sensor - IMU
Conn - Telemetry 1
